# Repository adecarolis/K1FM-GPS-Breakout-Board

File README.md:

# K1FM GPS Breakout Board

A simple breakout board for uBlox-M8 and SIM28M / SIM28ML chips.

Boards available at OSH Park: https://oshpark.com/shared_projects/maV0YvVP

## Changelog:

**Rev A**
Initial release

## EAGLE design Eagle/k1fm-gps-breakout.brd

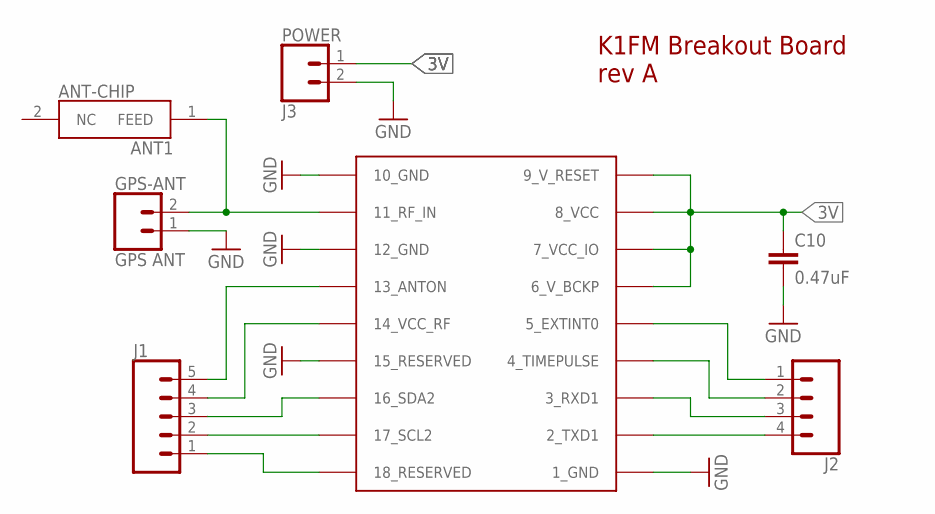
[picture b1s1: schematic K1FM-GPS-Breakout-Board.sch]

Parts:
ANT-CHIP: ANT1; 1575AT43A0040E
C10: 0.47uF; 0603
GPS1: UBLOX_MAX
GPS-ANT: GPS ANT; 1X02
J1: CONN_05; 1X05
J2: CONN_04; 1X04
J3: POWER; 1X02

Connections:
3V: C10.1, GPS1.6_V_BCKP, GPS1.7_VCC_IO, GPS1.8_VCC, GPS1.9_V_RESET, J3.1
GND: C10.2, GPS1.1_GND, GPS1.10_GND, GPS1.12_GND, GPS1.15_RESERVED, GPS-ANT.1, J3.2
unnamed: GPS1.4_TIMEPULSE, J2.2
unnamed: GPS1.3_RXD1, J2.3
unnamed: GPS1.2_TXD1, J2.4
unnamed: GPS1.5_EXTINT0, J2.1
unnamed: ANT-CHIP.1 (FEED), GPS1.11_RF_IN, GPS-ANT.2
unnamed: GPS1.18_RESERVED, J1.1
unnamed: GPS1.17_SCL2, J1.2
unnamed: GPS1.16_SDA2, J1.3
unnamed: GPS1.13_ANTON, J1.5
unnamed: GPS1.14_VCC_RF, J1.4

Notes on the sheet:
K1FM Breakout Board rev A

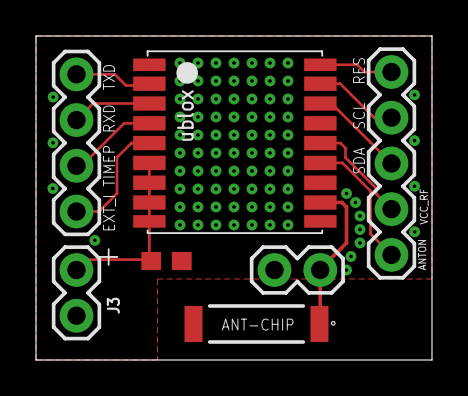
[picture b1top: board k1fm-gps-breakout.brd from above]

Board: 4 copper layers, 22.0 x 18.0 mm, 7 parts (0 on the bottom side), 12 nets.

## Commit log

2019-12-15 Add gitignore
2019-12-15 Add images
2019-12-15 Rename files
2019-12-15 Resize images
2019-12-15 Add readme
2019-12-15 Add OSH Park link

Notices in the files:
parts and their libraries:
SparkFun-Connectors: Licensing: Creative Commons ShareAlike 4.0 International - https://creativecommons.org/licenses/by-sa/4.0
